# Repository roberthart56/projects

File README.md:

# projects
rob's projects and log. 

[Digital Fabrication](./digital_fab)

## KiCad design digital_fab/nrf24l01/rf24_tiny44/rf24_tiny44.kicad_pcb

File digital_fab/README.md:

# Digital Fabrication

[Haystack 2024](./haystack_2024)
[Parametric Box](./parametric_box)
[Modular Things](./modular_things)

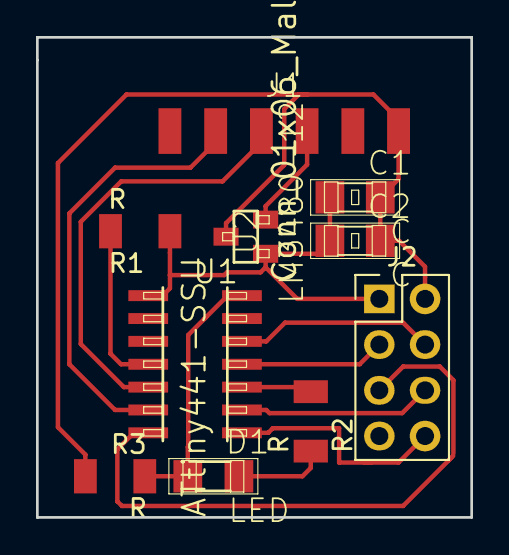
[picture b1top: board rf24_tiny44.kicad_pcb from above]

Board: 2 copper layers, 24.1 x 26.7 mm, 10 parts (0 on the bottom side), 13 nets.

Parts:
C1, C2: C; fab-C1206
D1: LED; fab-LED1206
J1: Conn_01x06_Male; fab-1X06SMD
J2: Conn_02x04_Odd_Even; PinHeader_2x04_P2.54mm_Vertical_modified
R1, R2, R3: R; fab-R1206FAB
U1: ATtiny441-SSU; fab-SOIC14
U2: LM3480-12; fab-SOT23

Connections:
CE: J2.4, U1.12
CSN: J2.3, U1.11
GND: C1.2, C2.2, D1.1, J1.1, J2.2, R3.1, R3.2, U1.14, U2.3
LED: R2.1, U1.10
MISO: J2.8, U1.8
MOSI: J2.5, U1.7
unnamed: D1.2, R2.2
unnamed: J1.3, U2.2
RST: R1.2, U1.4
RX: J1.4, U1.5
SCK: J2.6, U1.9
TX: J1.5, U1.6
VCC: C1.1, C2.1, J2.1, R1.1, U1.1, U2.1

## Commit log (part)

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2019-10-24 add nrf stuff
2019-12-02 add flash project and others
2019-12-30 various additions
2020-01-08 edited and remove stepper project
2020-02-02 moved stepper out and edited telophone
2020-02-02 edited telephone box
2020-02-02 update files for telephone
2020-02-04 added fiber and edited telephone
2020-02-11 edits to telephone
2020-02-13 edtis to index and figs.
2020-04-22 add samd folder
2020-06-30 moved telephone box
2020-08-26 add clank stuff
2020-11-17 edits
2020-11-17 add Nov 2020
2020-11-18 add programming folder
2020-11-21 Create README.md
    add cooking folder
2020-11-27 Rename README.md to readme.md
2020-12-08 add ubuntu project
2020-12-08 add december log file
2020-12-15 add vial lights
2021-01-02 added freecad
2021-01-02 added freecad readme
2021-01-06 test change
2021-01-06 change 2
2021-01-06 add vial pics
2021-01-06 add pics
2021-01-06 resize
2021-01-06 add jan
2021-01-08 added machines
2021-01-13 modify
2021-01-14 add freecad parametric
2021-01-14 remove
2021-01-15 Jan15
2021-01-15 add ender3
2021-01-18 add food proc repair
2021-01-18 try again
2021-01-19 python stuff
2021-01-19 knitting
2021-01-21 edit readme001
2021-01-21 edit readme
2021-01-22 add pic
2021-01-22 resizes
2021-01-22 edit
2021-01-25 added pics dir
2021-01-25 add figlist
2021-01-25 save
2021-01-25 rotate
2021-01-29 machine
2021-02-05 added pics
2021-02-11 add directory for cbd workflow
2021-02-18 add Feb
2021-02-26 add clavichord
2021-03-01 clav
2021-04-18 add reading
2021-04-18 caps
2021-06-03 airpump edit
2021-06-11 add smaller
2021-06-15 start organ page
2021-07-13 lkkj
2021-07-14 added code
2021-07-17 Create notes_7_16
2021-07-24 Create notes_7_24
2021-07-24 Update notes_7_24
2021-07-24 Rename notes_7_24 to notes_7_24.md
2021-07-24 Update notes_7_24.md
    attempt to add photo to markdown file
2021-07-28 added hall switch
2021-07-28 add picture and README
2021-07-28 edit1
2021-08-17 software
2021-08-17 new notes
2021-08-18 Create new_pictures_8_18.md
    new pictures
2021-08-18 Update new_pictures_8_18.md
    recent pictures added. Pedalboard with all sensors in place. half of the pedals are 'ribboned'. testing/calibrating imminent!
2021-08-19 add MIDI_Mega
2021-09-13 add programming links
2021-09-15 add kicad notes
2021-09-26 added garden
2022-01-20 update from windows
2022-01-20 add 2022 log
2022-01-20 edit log
2022-03-02 added error text
2022-03-02 add to text
2022-03-21 added sketch
2022-03-21 added pic
2022-07-07 add stuff
2022-11-10 add DICE folder
2023-02-02 add soil life
2023-03-28 add resonator
2023-03-28 edits and additions
2023-09-04 add haystack2023
2023-11-06 rearrange folders
2023-11-07 add material
2024-03-14 adding new folders
2024-08-27 various edits
2024-08-27 add maxl
2024-09-29 update changes
2024-11-12 added organ 2024
2024-12-05 add organ 2024 stuff
2025-01-20 edits and moving and Repair folder
2025-03-21 trying after reinstall
2026-02-17 added color clock
2026-02-17 added code and pic
2026-06-11 added clock pic
